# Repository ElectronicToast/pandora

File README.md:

TI SimpleLink CC2652R mesh network embedded system development board

## Description
Pandora is a development board for the TI SimpleLink CC2652R multiprotocol dual-core ARM wireless MCU designed for the Embedded System Design Laboratory course at Caltech (EE 110b). The board features interfaces for connecting a servo with analog feedback output and a [16x2 RGB-backlit LCD](https://www.adafruit.com/product/399). An onboard 16-key keypad and MPU-9250 IMU are provided for development use.

Pandora is intended to be powered from either an external 6-8.2V supply or a single-cell 3.7V LiPo battery. The former must be used to power the servo. A slide switch is used to select the power source. An onboard LiPo charger is present for charging through the USB-mini jack.

A TI SWRU120D 2.4GHz inverted-F PCB antenna is provided, in addition to a SMA jack for connecting an external 2.4GHz antenna. The antenna is selected using an 0603 two-way jumper.

This PCB is designed with KiCad v.5.1.5. Documentation may be found under `/doc`, and Gerbers under `/gerber`. 

## Author
- Ray Sun - Undergraduate, Electrical Engineering, Caltech, Class of 2020

## Licensing
This project is released under the terms of the MIT License. The SWRU120D antenna design is copyright 2007–2019, Texas Instruments Incorporated, and is used here for development of an application that uses a TI SimpleLink wireless microcontroller.

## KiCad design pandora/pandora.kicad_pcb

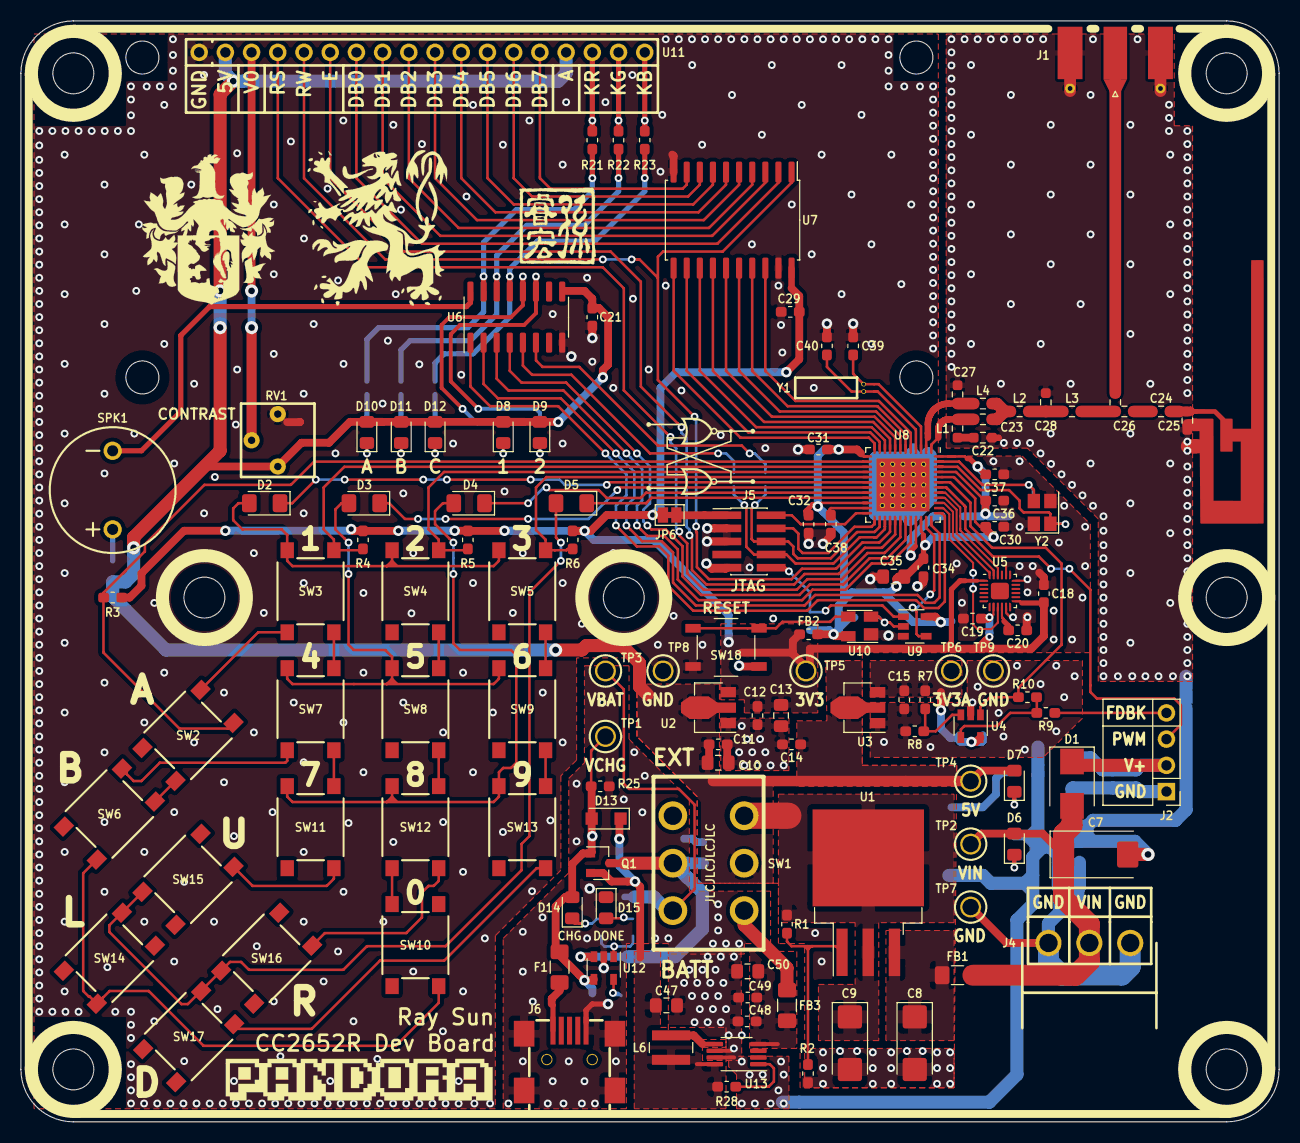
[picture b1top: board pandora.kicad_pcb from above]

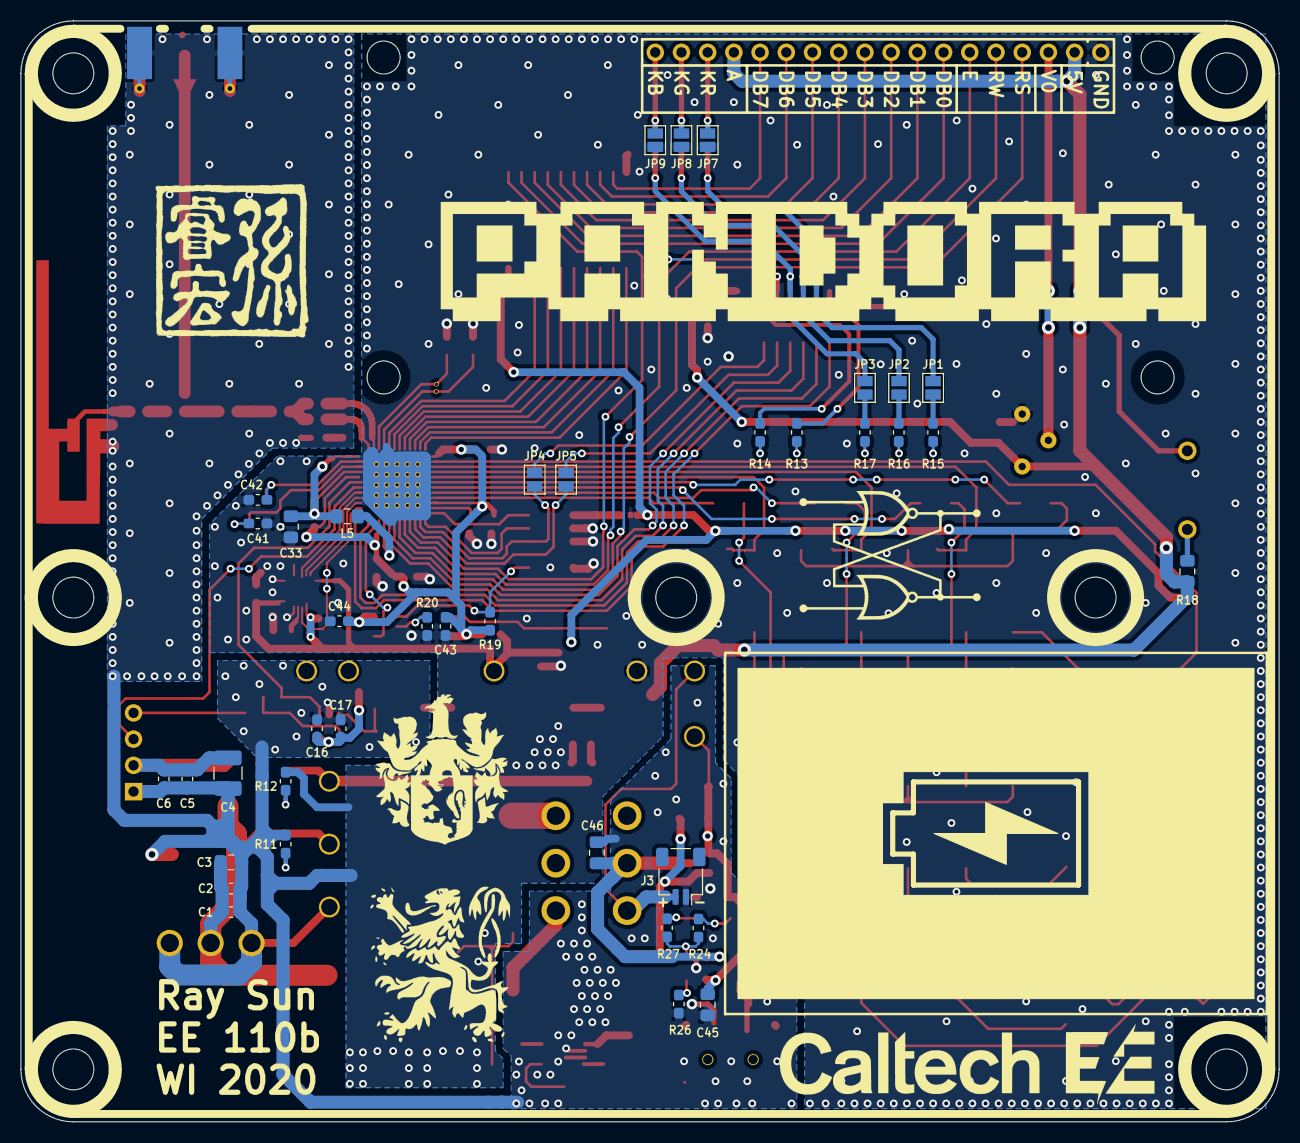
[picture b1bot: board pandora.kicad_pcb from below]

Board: 2 copper layers, 121.9 x 106.7 mm, 176 parts (43 on the bottom side), 121 nets.

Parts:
AE1: SWRU120D; Texas_SWRU120D_InvF_2.4GHz_Left
C1, C6, C16, C19, C20, C21, C29, C30, C31, C32, C34, C36, C37, C43, C44, C48: 0.1uF; C_0603_1608Metric_Pad1.05x0.95mm_HandSolder
C2, C5, C11, C12, C14, C15, C17, C38, C49: 1uF; C_0603_1608Metric_Pad1.05x0.95mm_HandSolder
C3, C13, C50: 10uF; C_0805_2012Metric_Pad1.15x1.40mm_HandSolder
C4: 47uF; C_1210_3225Metric_Pad1.42x2.65mm_HandSolder
C7: 47uF; CP_EIA-7343-31_Kemet-D
C8, C9: 10uF; CP_EIA-6032-28_Kemet-C_Pad2.25x2.35mm_HandSolder
C10, C33, C35: 22uF; C_0805_2012Metric_Pad1.15x1.40mm_HandSolder
C18: 10nF; C_0603_1608Metric_Pad1.05x0.95mm_HandSolder
C22: 12pF; 0603
C23, C27, C28: 1pF; 0603
C24: 1.8pF; 0603
C25: DNP; 0603
C26: 12pF; 0603_Branch
C39, C40: 15pF; C_0603_1608Metric_Pad1.05x0.95mm_HandSolder
C41, C42: 12pF; C_0603_1608Metric_Pad1.05x0.95mm_HandSolder
C45, C46, C47: 4.7uF; C_0805_2012Metric_Pad1.15x1.40mm_HandSolder
D1: S3JBHR5G; D_SMB
D2, D3, D4, D5: 1N4148; D_1206_3216Metric_Pad1.42x1.75mm_HandSolder
D6, D10: RED; LED_0805_2012Metric_Pad1.15x1.40mm_HandSolder
D7, D11, D15: GREEN; LED_0805_2012Metric_Pad1.15x1.40mm_HandSolder
D8, D9, D12: BLUE; LED_0805_2012Metric_Pad1.15x1.40mm_HandSolder
D13: PMEG10020ELRX; D_SOD-123W
D14: ORANGE; LED_0805_2012Metric_Pad1.15x1.40mm_HandSolder
F1: 0ZCJ0075FF2E; Fuse_1206_3216Metric_Pad1.42x1.75mm_HandSolder
FB1, FB3: 1206_4A; L_1206_3216Metric_Pad1.42x1.75mm_HandSolder
FB2: 0603_500mA; L_0603_1608Metric_Pad1.05x0.95mm_HandSolder
H1, H2, H3, H4, H5, H6, H7: #6; MountingHole_No6
J1: SMA; SMA_Molex_73251-1153_EdgeMount_Horizontal
J2: PinHeader_100mil_01x04; PinHeader_1x04_P2.54mm_Vertical
J3: JST-SH_2; JST_SH_SM02B-SRSS-TB_1x02-1MP_P1.00mm_Horizontal
J4: TX3 / MTA-156-3; TE_640389-3
J5: Conn_ARM_JTAG_SWD_10; PinHeader_2x05_P1.27mm_Vertical_SMD_Long
J6: USB_B_Mini; USB_MiniB_KMBSMT5SS30
JP1, JP2, JP3, JP4, JP5, JP7, JP8, JP9: SJ2; SolderJumper-2_P1.3mm_Open_Pad1.0x1.5mm
JP6: SJ2_Bridged; SolderJumper-2_P1.3mm_Bridged_Pad1.0x1.5mm
L1, L4: 2.4nH; 0603
L2, L3: 2nH; 0603
L5: 6.8uH; L_0805_2012Metric_Pad1.15x1.40mm_HandSolder
L6: 4.7uH; L_Wuerth_MAPI-4020
NT1, NT2, NT3, NT4, NT5: Net-Tie_2; NetTie-2_SMD_50mil
Q1: DMP1045U; SOT-23
R1, R12: 1.2k; R_0603_1608Metric_Pad1.05x0.95mm_HandSolder
R2: 3.6k; R_0603_1608Metric_Pad1.05x0.95mm_HandSolder
R3, R4, R5, R6, R19, R25, R26, R28: 10k; R_0603_1608Metric_Pad1.05x0.95mm_HandSolder
R7, R9: 150k; R_0603_1608Metric_Pad1.05x0.95mm_HandSolder
R8: 160k; R_0603_1608Metric_Pad1.05x0.95mm_HandSolder
R10: 120k; R_0603_1608Metric_Pad1.05x0.95mm_HandSolder
R11: 3.3k; R_0603_1608Metric_Pad1.05x0.95mm_HandSolder
R13: 330; R_0603_1608Metric_Pad1.05x0.95mm_HandSolder
R14, R17: 390; R_0603_1608Metric_Pad1.05x0.95mm_HandSolder
R15: 680; R_0603_1608Metric_Pad1.05x0.95mm_HandSolder
R16: 560; R_0603_1608Metric_Pad1.05x0.95mm_HandSolder
R18: 10; R_0805_2012Metric_Pad1.15x1.40mm_HandSolder
R20: 100k; R_0603_1608Metric_Pad1.05x0.95mm_HandSolder
R21, R22, R23: 0; R_0603_1608Metric_Pad1.05x0.95mm_HandSolder
R24, R27: 1k; R_0603_1608Metric_Pad1.05x0.95mm_HandSolder
RV1: 10k; Pot_VR4_Small
SPK1: DBX-01PN
SW1: GF-126-0317
SW2, SW3, SW4, SW5, SW6, SW7, SW8, SW10, SW11, SW12: PTS645-S-H-50-SMTR92-LFS; SW_Push_PTS645_SMT
SW9, SW13: PTS645-S-M-43-SMTR92-LFS; SW_Push_PTS645_SMT
SW14, SW15, SW16, SW17: PTS645-S-K-50-SMTR92-LFS; SW_Push_PTS645_SMT
SW18: PTS526-S-K-15-SMTR92; SW_Push_PTS526
TP1, TP2, TP3, TP4, TP5, TP6, TP7, TP8, TP9: TestPoint; TestPoint_62-80mil
U1: LM1086CS-ADJ; TO-263-3_TabPin2
U2, U3: MCP1702T-3302; SOT-89-3
U4: MCP6001; SOT-23-5
U5: MPU-9250; MPU-9250_Wide
U6: ULN2003D; SOIC-16_3.9x9.9mm_P1.27mm
U7: 74LCX245; SOIC-20W_7.5x12.8mm_P1.27mm
U8: CC2652R; Texas_RGZ0048A_Wide
U9: 74LVC1G08; SOT-23-5
U10: ADM811ZARTZ; SOT-143
U11: LCD_Adafruit_16x02_Neg_RGB
U12: MCP73831-2-OT; SOT-23-5
U13: MCP1642D-50; MSOP-8_3x3mm_P0.65mm
Y1: NC26_32.768k; NC26H_Mirrored
Y2: FA-238_48M; Crystal_SMD_SeikoEpson_FA238-4Pin_3.2x2.5mm

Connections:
+3.3VA: C15.1, C16.1, C17.1, R7.1, TP6.1, U3.3, U4.5
+3V3: C12.1, C13.1, C18.1, C19.2, C29.2, FB2.2, JP6.1, R3.1, R4.1, R5.1, R6.1, TP5.1, U2.3, U5.1, U5.8, U5.13, U7.20
+5V: C10.1, C11.1, C14.1, C21.2, D7.2, D8.2, D9.2, D10.2, D11.2, D12.2, R18.2, RV1.1, SW1.2, TP4.1, U2.2, U3.2, U6.9, U11.2, U11.15
/battery/VLV: C47.1, D13.1, L6.1, Q1.2, R28.2, U13.8
/connectors/JTAG_TCK: J5.4, U8.25
/connectors/JTAG_TDI: J5.8, JP5.1, U8.27
/connectors/JTAG_TDO: J5.6, JP4.1, U8.26
/connectors/JTAG_TMS: J5.2, U8.24
/connectors/JTAG_~RESET: J5.10, R19.2, U9.1
/connectors/LCD_OUT_BL_B: JP3.2, R23.1, U6.13
/connectors/LCD_OUT_BL_G: JP2.2, R22.1, U6.14
/connectors/LCD_OUT_BL_R: JP1.2, R21.1, U6.15
/connectors/LCD_OUT_CNTR: RV1.2, U11.3
/connectors/LCD_OUT_DB0: U7.2, U11.7
/connectors/LCD_OUT_DB1: U7.3, U11.8
/connectors/LCD_OUT_DB2: U7.4, U11.9
/connectors/LCD_OUT_DB3: U7.5, U11.10
/connectors/LCD_OUT_DB4: U7.6, U11.11
/connectors/LCD_OUT_DB5: U7.7, U11.12
/connectors/LCD_OUT_DB6: U7.8, U11.13
/connectors/LCD_OUT_DB7: U7.9, U11.14
/connectors/LCD_OUT_RS: U8.30, U11.4
/connectors/LCD_OUT_RW: U7.1, U8.28, U11.5
/connectors/SERVO_PWM: J2.3, U8.42
/imu/IMU_MISO: U5.9, U8.38
/imu/IMU_MOSI: U5.24, U8.39
/imu/IMU_SCK: U5.23, U8.40
/imu/IMU_~CS: U5.22, U8.41
/keypad/KPD_IN1: R3.2, SW2.2, SW6.2, SW10.2, SW14.2, U8.14
/keypad/KPD_IN2: R4.2, SW3.2, SW7.2, SW11.2, SW15.2, U8.15
/keypad/KPD_IN3: R5.2, SW4.2, SW8.2, SW12.2, SW16.2, U8.16
/keypad/KPD_IN4: R6.2, SW5.2, SW9.2, SW13.2, SW17.2, U8.17
/keypad/KPD_OUT1: D2.1, U8.18
/keypad/KPD_OUT2: D3.1, U8.19
/keypad/KPD_OUT3: D4.1, U8.20
/keypad/KPD_OUT4: D5.1, U8.21
/lcd/LCD_DB0: U7.18, U8.5
/lcd/LCD_DB1: U7.17, U8.6
/lcd/LCD_DB2: U7.16, U8.7
/lcd/LCD_DB3: U7.15, U8.8
/lcd/LCD_DB4: U7.14, U8.9
/lcd/LCD_DB5: U7.13, U8.10
/lcd/LCD_DB6: U7.12, U8.11
/lcd/LCD_DB7: U7.11, U8.12
/lcd/LCD_E: U8.29, U11.6
/led_speaker/LCD_BL_B: U6.4, U8.31
/led_speaker/LCD_BL_G: U6.3, U8.32
/led_speaker/LCD_BL_R: U6.2, U8.36
/led_speaker/LED1: JP5.2, U6.5
/led_speaker/LED1_DRV: R13.2, U6.12
/led_speaker/LED2: JP4.2, U6.6
/led_speaker/LED2_DRV: R14.2, U6.11
/led_speaker/LEDA_DRV: JP1.1, R15.2
/led_speaker/LEDB_DRV: JP2.1, R16.2
/led_speaker/LEDC_DRV: JP3.1, R17.2
/led_speaker/SPEAKER: U6.1, U8.37
/led_speaker/SPK_DRV: SPK1.2, U6.16
/mcu/DCDC_SW: L5.1, U8.33
/mcu/RF_N: C27.1, L4.1, U8.2
/mcu/RF_P: C23.2, L1.2, U8.1
/mcu/VMCUA: C33.1, C36.2, C37.2, L5.2, U8.45, U8.48
/mcu/~RESET: U8.35, U9.4
/servo/AIN: R10.1, U4.1, U8.43
/servo/FDBK: J2.4, R9.2
/servo/VREF: R7.2, R8.1, U4.3
GNDA: C15.2, C16.2, C17.2, NT2.2, R8.2, TP9.1, U3.1, U4.2
GNDBAT: C45.2, C46.2, C47.2, C48.2, C49.2, C50.2, D15.1, J3.1, J6.5, J6.6, NT5.2, R25.1, R26.1, U12.2, U13.6, U13.7
GNDD: C8.2, C9.2, C10.2, C11.2, C12.2, C13.2, C14.2, C18.2, C19.1, C20.1, C21.1, C29.1, C30.1, C31.1, C32.1, C33.2, C34.1, C35.1, C36.1, C37.1, C38.1, C39.1, C40.2, C41.1, C42.2, C43.2, C44.1, J5.3, J5.5, J5.9, JP7.2, JP8.2, JP9.2, NT1.2, R2.2, R12.2, R20.2, RV1.3, SW18.1, TP8.1, U2.1, U5.11, U5.18, U5.20, U6.8, U7.10, U7.19, U8.49, U9.3, U10.1, U11.1, Y2.2, Y2.4
GNDIN: C1.2, C2.2, C3.2, C7.2, J4.1, J4.3, NT1.1, NT2.1, NT3.1, NT4.1, NT5.1, R11.2, TP7.1
GNDRF: AE1.2, C22.1, C25.2, C27.2, C28.2, J1.2, NT3.2
GNDSERVO: C4.2, C5.2, C6.2, J2.1, NT4.2
unnamed: AE1.1, C24.1, C25.1
unnamed: C8.1, FB1.1, U1.3
unnamed: C9.1, R1.1, SW1.1, U1.2
unnamed: C20.2, U5.10
unnamed: C22.2, L1.1
unnamed: C23.1, L2.1, L4.2
unnamed: C24.2, C26.2
unnamed: C26.1, L3.2
unnamed: C26.3, J1.1
unnamed: C28.1, L2.2, L3.1
unnamed: C38.2, U8.23
unnamed: C39.2, U8.3, Y1.1
unnamed: C40.1, U8.4, Y1.2
unnamed: C41.2, U8.46, Y2.1
unnamed: C42.1, U8.47, Y2.3
unnamed: C46.1, Q1.3, SW1.5, U12.3
unnamed: C48.1, C49.1, C50.1, FB3.2, U13.4
unnamed: D2.2, SW2.1, SW3.1, SW4.1, SW5.1
unnamed: D3.2, SW6.1, SW7.1, SW8.1, SW9.1
unnamed: D4.2, SW10.1, SW11.1, SW12.1, SW13.1
unnamed: D5.2, SW14.1, SW15.1, SW16.1, SW17.1
unnamed: D6.1, R11.1
unnamed: D7.1, R12.1
unnamed: D8.1, R13.1
unnamed: D9.1, R14.1
unnamed: D10.1, R15.1
unnamed: D11.1, R16.1
unnamed: D12.1, R17.1
unnamed: D14.1, R24.1
unnamed: D15.2, R27.1
unnamed: F1.1, J6.1
unnamed: J5.1, JP6.2
unnamed: JP7.1, R21.2, U11.16
unnamed: JP8.1, R22.2, U11.17
unnamed: JP9.1, R23.2, U11.18
unnamed: L6.2, U13.5
unnamed: R1.2, R2.1, U1.1
unnamed: R9.1, R10.2, U4.4
unnamed: R18.1, SPK1.1
unnamed: R20.1, U9.2, U10.2
unnamed: R24.2, R27.2, U12.1
unnamed: R26.2, U12.5
unnamed: R28.1, U13.1
unnamed: SW18.2, U10.3
VBAT: J3.2, SW1.6, TP3.1
VBOOST: FB3.1, SW1.3
VCHG: C45.1, D13.2, D14.2, F1.2, Q1.1, R25.2, TP1.1, U12.4
VIN: C1.1, C2.1, C3.1, C7.1, D1.2, D6.2, FB1.2, J4.2, TP2.1
VMCU: C30.2, C31.2, C32.2, C34.2, C35.2, C43.1, C44.2, FB2.1, R19.1, U8.13, U8.22, U8.34, U8.44, U9.5, U10.4
VSERVO: C4.1, C5.1, C6.1, D1.1, J2.2

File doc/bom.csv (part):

Designator,Value,FootprintRef,Datasheet,Comment,Footprint,PartNo,Supplier,SupplierPartNo,Qty
    AE1,SWRU120D,pandora:Texas_SWRU120D_InvF_2.4GHz_Left,http://www.ti.com/lit/an/swru120d/swru120d.pdf,PCB antenna,SWRU120D,N/A,N/A,N/A,1
">  C1, C6, C16, C19-C21, C29-C32, C34, C36, C37, C43, C44, C48",0.1uF,Capacitor_SMD:C_0603_1608Metric_Pad1.05x0.95mm_HandSolder,~,,603,,In House,N/A,16
    C4,47uF,Capacitor_SMD:C_1210_3225Metric_Pad1.42x2.65mm_HandSolder,~,,805,,In House,N/A,1
    C7,47uF,Capacitor_Tantalum_SMD:CP_EIA-7343-31_Kemet-D,https://content.kemet.com/datasheets/KEM_T2005_T491.pdf,25V,2917,T491D476M025AT,Digi-Key,399-3797-1-ND,1
">  C8, C9",10uF,Capacitor_Tantalum_SMD:CP_EIA-6032-28_Kemet-C_Pad2.25x2.35mm_HandSolder,http://datasheets.avx.com/trj.pdf,35V,2312,TRJC106K035R0600,Digi-Key,478-7582-1-ND,2
">  C10, C33, C35",22uF,Capacitor_SMD:C_0805_2012Metric_Pad1.15x1.40mm_HandSolder,~,,805,,In House,N/A,3
">  C2, C5, C11, C12, C14, C15, C17, C38, C49",1uF,Capacitor_SMD:C_0603_1608Metric_Pad1.05x0.95mm_HandSolder,~,,603,,In House,N/A,9
">  C3, C13, C50",10uF,Capacitor_SMD:C_0805_2012Metric_Pad1.15x1.40mm_HandSolder,~,,805,,In House,N/A,3
    C18,10nF,Capacitor_SMD:C_0603_1608Metric_Pad1.05x0.95mm_HandSolder,~,,603,,In House,N/A,1
    C22,12pF,pandora:0603,~,,603,,In House,N/A,1
    C24,1.8pF,pandora:0603,~,,603,,In House,N/A,1
    C25,DNP,pandora:0603,~,,603,,In House,N/A,1
    C26,12pF,pandora:0603_Branch,~,,0603-2way,,In House,N/A,1
">  C23, C27, C28",1pF,pandora:0603,~,,603,,In House,N/A,3
">  C39, C40",15pF,Capacitor_SMD:C_0603_1608Metric_Pad1.05x0.95mm_HandSolder,~,,603,,In House,N/A,2
">  C41, C42",12pF,Capacitor_SMD:C_0603_1608Metric_Pad1.05x0.95mm_HandSolder,~,,603,,In House,N/A,2
>  C45-C47,4.7uF,Capacitor_SMD:C_0805_2012Metric_Pad1.15x1.40mm_HandSolder,~,,805,,In House,N/A,3
    D1,S3JBHR5G,Diode_SMD:D_SMB,https://www.onsemi.com/pub/Collateral/1N5400-D.PDF,3A,SMB,S3JBHR5G,Digi-Key,S3JBHR5GCT-ND,1
>  D2-D5,1N4148,Diode_SMD:D_1206_3216Metric_Pad1.42x1.75mm_HandSolder,https://www.diodes.com/assets/Datasheets/ds30086.pdf,,1206 / SOD-123,,In House,N/A,4
">  D6, D10",RED,LED_SMD:LED_0805_2012Metric_Pad1.15x1.40mm_HandSolder,~,,805,,In House,N/A,2
">  D7, D11, D15",GREEN,LED_SMD:LED_0805_2012Metric_Pad1.15x1.40mm_HandSolder,~,,805,,In House,N/A,3
">  D8, D9, D12",BLUE,LED_SMD:LED_0805_2012Metric_Pad1.15x1.40mm_HandSolder,~,,805,,In House,N/A,3
    D13, PMEG10020ELRX,pandora:D_SOD-123W,https://assets.nexperia.com/documents/data-sheet/PMEG10020ELR.pdf,,SOD-123W,PMEG10020ELRX,Digi-Key,1727-2396-1-ND,1
    D14,ORANGE,LED_SMD:LED_0805_2012Metric_Pad1.15x1.40mm_HandSolder,~,,805,,In House,N/A,1
    F1, 0ZCJ0075FF2E,Fuse:Fuse_1206_3216Metric_Pad1.42x1.75mm_HandSolder,https://www.belfuse.com/resources/datasheets/circuitprotecti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,"Charging input fuse, 750mA hold",1206,0ZCJ0075FF2E,Digi-Key,507-1804-1-ND,1
">  FB1, FB3",1206_4A,Inductor_SMD:L_1206_3216Metric_Pad1.42x1.75mm_HandSolder,https://ds.yuden.co.jp/TYCOMPAS/ut/detail?pn=BKP2125HS600-T%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,,1206,FBMJ3216HS800-T,Digi-Key,587-1772-1-ND,2
    FB2,0603_500mA,Inductor_SMD:L_0603_1608Metric_Pad1.05x0.95mm_HandSolder,https://ds.yuden.co.jp/TYCOMPAS/ut/detail?pn=BKP1608HS391-T%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,,603,BKP1608HS391-T,Digi-Key,587-1927-1-ND,1
>  H1-H7,#6,pandora:MountingHole_No6,~,"#6 mounting hole, NPTH",HOLE_156mil_NPTH,N/A,N/A,N/A,7
    J1,SMA,Connector_Coaxial:SMA_Molex_73251-1153_EdgeMount_Horizontal,https://www.molex.com/pdm_docs/sd/732511153_sd.pdf,External antenna connector,SMA_SMD_RightAngle,732511150,Molex,732511150,1
    J2,PinHeader_100mil_01x04,Connector_PinHeader_2.54mm:PinHeader_1x04_P2.54mm_Vertical,~,Servo connector,100mil_01x04,,In House,N/A,1
    J3,JST-SH_2,Connector_JST:JST_SH_SM02B-SRSS-TB_1x02-1MP_P1.00mm_Horizontal,~,JST SH auxiliary Li-ion connector,JST-SH_SM_2_SMD_RghtAngle,,In House,N/A,1
    J4,TX3 / MTA-156-3,pandora:TE_640389-3,~,156mil 3-pin power connector,156mil_01x03,,In House,N/A,1
    J5,Conn_ARM_JTAG_SWD_10,pandora:PinHeader_2x05_P1.27mm_Vertical_SMD_Long,http://infocenter.arm.com/help/topic/com.arm.doc.ddi0314h/DD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,JTAG debug header,50mil_02x05,FTSH-105-0.1-F-DV-K,In House,N/A,1
    J6,USB_B_Mini,pandora:USB_MiniB_KMBSMT5SS30,~,5V battery charge connector,KMBSMT5SS30,KMBSMT5SS30,In House,N/A,1
">  JP1-JP5, JP7-JP9",SJ2,Jumper:SolderJumper-2_P1.3mm_Open_Pad1.0x1.5mm,~,"Solder jumper, 2 pad",SMD_PAD_SJ2,N/A,N/A,N/A,8
    JP6,SJ2_Bridged,Jumper:SolderJumper-2_P1.3mm_Bridged_Pad1.0x1.5mm,~,"Solder jumper, 2 pad, bridged",SMD_PAD_SJ2_Bridged,N/A,N/A,N/A,1
">  L2, L3",2nH,pandora:0603,~,,603,,In House,N/A,2
">  L1, L4",2.4nH,pandora:0603,~,,603,,In House,N/A,2
    L5,6.8uH,Inductor_SMD:L_0805_2012Metric_Pad1.15x1.40mm_HandSolder,https://product.tdk.com/info/en/catalog/datasheets/inductor_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,MCU analog filter inductor,805,MLZ2012N6R8LTD25,Digi-Key,445-16384-1-ND,1
    L6,4.7uH,Inductor_SMD:L_Wuerth_MAPI-4020,https://www.we-online.com/catalog/datasheet/74438356047.pdf,Power inductor for boost converter,Wuerth_MAPI-4020,74438356047,Digi-Key,732-8234-1-ND,1
>  NT1-NT5,Net-Tie_2,pandora:NetTie-2_SMD_50mil,~,,N/A,N/A,N/A,N/A,5
    Q1,DMP1045U,Package_TO_SOT_SMD:SOT-23,https://www.diodes.com/assets/Datasheets/DMP1045U.pdf,Load sharing P-MOSFET,SOT-23,DMP1045U-7,Digi-Key,DMP1045U-7DICT-ND,1
">  R1, R12",1.2k,Resistor_SMD:R_0603_1608Metric_Pad1.05x0.95mm_HandSolder,~,,603,,In House,N/A,2
    R2,3.6k,Resistor_SMD:R_0603_1608Metric_Pad1.05x0.95mm_HandSolder,~,,603,,In House,N/A,1
">  R3-R6, R19, R25, R26, R28",10k,Resistor_SMD:R_0603_1608Metric_Pad1.05x0.95mm_HandSolder,~,,603,,In House,N/A,8
    R8,160k,Resistor_SMD:R_0603_1608Metric_Pad1.05x0.95mm_HandSolder,~,,603,,In House,N/A,1
">  R7, R9",150k,Resistor_SMD:R_0603_1608Metric_Pad1.05x0.95mm_HandSolder,~,,603,,In House,N/A,2
    R10,120k,Resistor_SMD:R_0603_1608Metric_Pad1.05x0.95mm_HandSolder,~,,603,,In House,N/A,1
    R11,3.3k,Resistor_SMD:R_0603_1608Metric_Pad1.05x0.95mm_HandSolder,~,,603,,In House,N/A,1
    R13,330,Resistor_SMD:R_0603_1608Metric_Pad1.05x0.95mm_HandSolder,~,,603,,In House,N/A,1
">  R14, R17",390,Resistor_SMD:R_0603_1608Metric_Pad1.05x0.95mm_HandSolder,~,,603,,In House,N/A,2
    R15,680,Resistor_SMD:R_0603_1608Metric_Pad1.05x0.95mm_HandSolder,~,,603,,In House,N/A,1
    R16,560,Resistor_SMD:R_0603_1608Metric_Pad1.05x0.95mm_HandSolder,~,,603,,In House,N/A,1
    R18,10,Resistor_SMD:R_0805_2012Metric_Pad1.15x1.40mm_HandSolder,~,Speaker power resistor,805,,In House,N/A,1
    R20,100k,Resistor_SMD:R_0603_1608Metric_Pad1.05x0.95mm_HandSolder,~,,603,,In House,N/A,1
>  R21-R23,0,Resistor_SMD:R_0603_1608Metric_Pad1.05x0.95mm_HandSolder,~,,603,,In House,N/A,3
">  R24, R27",1k,Resistor_SMD:R_0603_1608Metric_Pad1.05x0.95mm_HandSolder,~,,603,,In House,N/A,2
    RV1,10k,pandora:Pot_VR4_Small,https://www.bourns.com/docs/Product-Datasheets/TC33.pdf,LCD contrast potentiometer,Bourns_TC33,TC33X-2-103E,Digi-Key,TC33X-103ECT-ND,1
    SPK1,DBX-01PN,pandora:DBX-01PN,~,"Speaker, board mount",DBX-01PN,DBX-01PN,In House,DBX-01PN,1
    SW1,GF-126-0317,pandora:GF-126-0317,https://media.digikey.com/pdf/Data%20Sheets/CW%20Industries%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,Power switch,GF-126-037,GF-126-037,Digi-Key,CWI351-ND,1
">  SW2-SW8, SW10-SW12",PTS645-S-H-50-SMTR92-LFS,pandora:SW_Push_PTS645_SMT,https://dznh3ojzb2azq.cloudfront.net/products/Tactile/PTS645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,"Keypad button, black",Tact_Push_SMD_6mm,PTS645SH50SMTR92 LFS,Digi-Key,CKN9085CT-ND,10
">  SW9, SW13",PTS645-S-M-43-SMTR92-LFS,pandora:SW_Push_PTS645_SMT,https://dznh3ojzb2azq.cloudfront.net/products/Tactile/PTS645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,"Keypad button, blue",Tact_Push_SMD_6mm,PTS645SM43SMTR92 LFS,Digi-Key,CKN9112CT-ND,2
>  SW14-SW17,PTS645-S-K-50-SMTR92-LFS,pandora:SW_Push_PTS645_SMT,https://dznh3ojzb2azq.cloudfront.net/products/Tactile/PTS645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,"Keypad button, red",Tact_Push_SMD_6mm,PTS645SK50SMTR92 LFS,Digi-Key,CKN9087CT-ND,4
    SW18,PTS526-S-K-15-SMTR92,pandora:SW_Push_PTS526,https://dznh3ojzb2azq.cloudfront.net/products/Tactile/PTS526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,Reset button,Tact_Push_SMD_PTS526,PTS526SK15SMTR92 LFS,In House,PTS526SK15SMTR92 LFS,1
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
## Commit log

2020-01-17 Make project
2020-01-17 Make CC2652R symbol and footprint
2020-01-17 Start schematic
2020-01-25 Create subsheets
2020-01-25 Align CC2652R symbol with 100 mil grid
2020-01-25 Rename library
2020-01-25 Begin laying out hierarchial connections
2020-01-27 Add IMU pins
2020-01-30 Continue schematic design
2020-01-30 Select supervisor IC
2020-01-30 Lay out servo and IMU
2020-01-31 Add battery holder symbols
2020-01-31 Restore load caps
2020-01-31 Redesign reset circuit
2020-02-01 Revise to use Adafruit negative backlight LCD with ULN2003 driver
2020-02-01 Expose LCD contrast on separate label
2020-02-01 Add Adafruit 16x02 RGB negative backlight LCD symbol and footprint
2020-02-01 Add LCD and connectors
2020-02-01 Fix keypad diode direction
2020-02-01 Add resistor to prevent contention between JTAG reset and supervisor
2020-02-02 Fix pinout and add auxiliary LEDs to TDI/TDO
2020-02-02 Find servo amp resistor values
2020-02-03 Power LCD level shifter from 3V3
2020-02-04 Add MCP1702 symbol
2020-02-04 Add LM1086 symbol
2020-02-04 Add LCD footprint with both rows of pins
2020-02-04 Remove LCD holes from mechanical
2020-02-04 Add solder jumpers to select between backlight PWM and ground
2020-02-04 Add RF jumper symbols
2020-02-05 Make power symbols
2020-02-05 Improve symbol fields
2020-02-06 Add solder jumpers to disconnect or select RGB backlight output
2020-02-07 Change speaker resistr to 1206
2020-02-07 Connect power switch properly
2020-02-07 Add LT1935 boost converter symbol
2020-02-07 Design boost converter
2020-02-07 Select slide switch
2020-02-07 Begin redesigning reset circuit
2020-02-07 Select contrast potentiometer
2020-02-07 Edit battery holder / switch package fields
2020-02-07 Change 10uF bulk caps to 22uF
2020-02-07 Change some capacitors to take advantage of in house sizes
2020-02-07 Reorder subsheets
2020-02-07 Make project logo
2020-02-07 Add logo to top level sheet
2020-02-07 Create ADM811 reset supervisor symbol
2020-02-07 Design reset supervisor
2020-02-07 Update layout
2020-02-08 Spec speaker
2020-02-08 Add page layout description file
2020-02-08 Select pushbuttons
2020-02-08 Make better antenna symbol
2020-02-08 Add antenna symbol with ground
2020-02-09 Fix VDDR, VDDRF as power input pins
2020-02-09 Annotate schematic; need to reconnect without heterogeneous busses
2020-02-09 Generate schematic
2020-02-09 Generate preliminary BOM
2020-02-09 Redesign hierarchial interconnections
2020-02-09 Pass ERC without errors
2020-02-09 Make V-charge symbol
2020-02-09 Design battery charger circuit (need connector)
2020-02-09 Fix load share
2020-02-10 Add USB connector for charging
2020-02-10 Add MCP1642 symbol
2020-02-10 Design new boost converter
2020-02-10 Update symbol fields
2020-02-10 Choose speaker
2020-02-10 Move hidden pin on MCP1642 up
2020-02-10 Annotate and regenerate docs
2020-02-10 Consider not needing boost converter bypass
2020-02-10 Remove incorrect bypass disable
2020-02-10 Fuse charging input and remove alternative aux battery conector
2020-02-11 Remove ferrite beads from ground paths
2020-02-11 Remove bypass feature and add extra caps to boost output to help stability
2020-02-11 Change values on load share circuit
2020-02-11 Make speaker footprint
2020-02-11 Add auxiliary battery switch
2020-02-11 Spec boost inductor (Wuerth MAPI)
2020-02-11 Update reset supervisor footprint
2020-02-11 Make NC26 crystal footprint
2020-02-11 Add LCD footprint comments
2020-02-11 Fix servo pin header order
2020-02-11 Make PTS645 footprint
2020-02-11 Add local footprint folter gitignore
2020-02-11 Update some symbol fields
2020-02-11 Add supplier fields to symbols
2020-02-12 Find switch part numbers
2020-02-12 Rename button footprints and select reset button
2020-02-12 Reannotate by Y position for more sensible keypad
2020-02-12 Update supplier fields
2020-02-12 Clean up
2020-02-12 Spec MCU analog power filter inductor
2020-02-12 Add auxiliary LEDs to backlight lines with jumpers
2020-02-13 Add silkscreen zone footprints for battery
2020-02-13 Pick correct battery connector
2020-02-13 Make right angle MTA-156 footprint (need to verify)
2020-02-13 Make MiniUSB footprint
2020-02-13 Select SMA connector
2020-02-13 Adjust dimensions and make branch footprint
2020-02-13 Update 0402 ffootprint ields
2020-02-13 Make long JTAG header footprint
2020-02-14 Tidy up
2020-02-18 Add test points
2020-02-18 Redesign LED jumpers to cut down on components
2020-02-18 Reorganize power section
2020-02-18 Add potentiometer footprints
2020-02-18 Reorganize power into two sheets
2020-02-19 Add VBOOST power port
2020-02-19 Add more handsoldering holes for power pad
2020-02-19 Make IMU footprint with wide pads
2020-02-19 Update footprints on schematic
2020-02-19 Correct 22uF ceramic sizes to 0805
2020-02-25 Change 1N4148 footprint to 1206
2020-02-26 Change servo drop diode to SMD package (SMB)
2020-02-27 Spec DPDT switch and FBs
2020-02-27 Make antenna footprint
2020-02-27 Start layout
2020-02-28 Begin layout
2020-02-28 Continue layout
2020-02-28 Continue layout (CPWG width needs to be defined)
2020-02-29 Add 15 mil stitch via
2020-03-02 Replace speaker resistor with 0805
2020-03-02 Make #6 mounting holes
2020-03-04 Add imperial size net tie footprints
2020-03-04 Start routing
2020-03-05 Almost finish routing
2020-03-06 Finish routing
2020-03-06 Generate preliminary Gerbers and BOM
2020-03-07 Fix top silk
2020-03-07 Fix bottom silk
2020-03-07 Decorate
2020-03-07 Move things around
2020-03-07 Make schematic size ANSI A
2020-03-07 Continue decorating
2020-03-08 Add 0603 branch footprint
2020-03-08 Replace RF components with 0603
2020-03-08 Make square 0603 footprint
2020-03-08 Re-make RF section
2020-03-08 Stitch RF plane and decorate
2020-03-08 Fix planes
2020-03-09 Regenerate project output
2020-03-09 Fix silkscreen
2020-03-09 Fix FA-238 and 10uF tant footprints
2020-03-09 Rearrange 10uF tants
2020-03-09 Fix MCP1702 pinout
2020-03-09 Update BOM
2020-03-09 Fix some FreeDFM issues
2020-03-09 Fix RF top ground zone
2020-03-09 Add local 3D models and make small aesthetical changes
2020-03-11 Generate Gerbers without NO ADDITIONAL COPPER on edge layer
2020-03-21 Clean up analog trace and ground spacing
2020-03-21 Make CC2652R pad holes 12mil
2020-03-21 Actually use wider VQFN footprints
2020-03-21 Replace pot with THT one, and add aesthetics
2020-03-21 Regenerate Gerbers and BOM
2020-03-24 Move R25 to top to avoid battery connector and move designators around
2020-03-24 Generate production files
2020-03-24 Clean up schematic
2020-03-24 Move antenna footprint image
2020-03-24 Generate board renders
2020-03-24 Fix reset button on schematic
2020-03-24 Fix license badge
